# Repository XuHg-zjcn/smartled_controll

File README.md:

# 智能LED控制器
该LED控制器用于吸顶灯、灯带、台灯的控制，使用12-48V电源供电(使用Buck驱动，电源电压必须高于灯的电压)，使用经过编码的RS485通信。计划PCB采用双面板，板上最多可焊4个LED驱动电路
待添加多种设计，分别支持4通道和2通道
需要添加外接声感（驻极体麦克风），雷达，（热释电）红外线等传感器检测下亮灯

经过平衡安全性、稳定性、传输效率、可扩展性、总成本等因素的考量，我设计家庭小功率电器总线采用不超过直流60V的SELV供电。使用两根直流电源线（不接地）和一对差分通信线。  
为了防止通信线(RS485)误接电源线造成过压等原因导致芯片等元器件损坏，我参考网上资料设计了一套保护电路。其中甚至牺牲了一些兼容性，让数据经过直流平衡的编码后再传输，这样信号能顺利通过电容，误接直流电时后面电路只有一个脉冲，大大减轻TVS管负荷。  

# 主要元器件列表
|  名称  |     型号     |    参数     |
|:------:|:-------------|:------------|
|MCU     |候选PY32F003F1|QFN20封装    |
|DCDC转换|OC5864        |最高60V输入, 0.6A|
|LED驱动 |OC5028B/OC5020B|100V 1.2A/2A|
|通信芯片|候选MAX485    |最高2.5Mbps  |

其他元器件请通过KiCAD生成BOM表获取

# 构建PCB工程
为了减少git仓库占用空间，我在`git commit`提交前在KiCad中清除所有填充域(快捷键Ctrl+B)，您可以在打开后重新填充(快捷键B)
在KiCad的Python控制台中，切换到该repo根目录运行下例命令
````python
import build
build.all()
```
即可自动完成添加泪滴、重新填充、应用PCB背面信息字符串

# 版权和许可证
Copyright (C) 2025  徐瑞骏  
本设计以CERN开放硬件许可证第二版强互惠授权(CERN Open Hardware Licence Version 2 - Strongly Reciprocal)，许可证文件位于`cern_ohl_s_v2.txt`  
本设计不提供任何保证

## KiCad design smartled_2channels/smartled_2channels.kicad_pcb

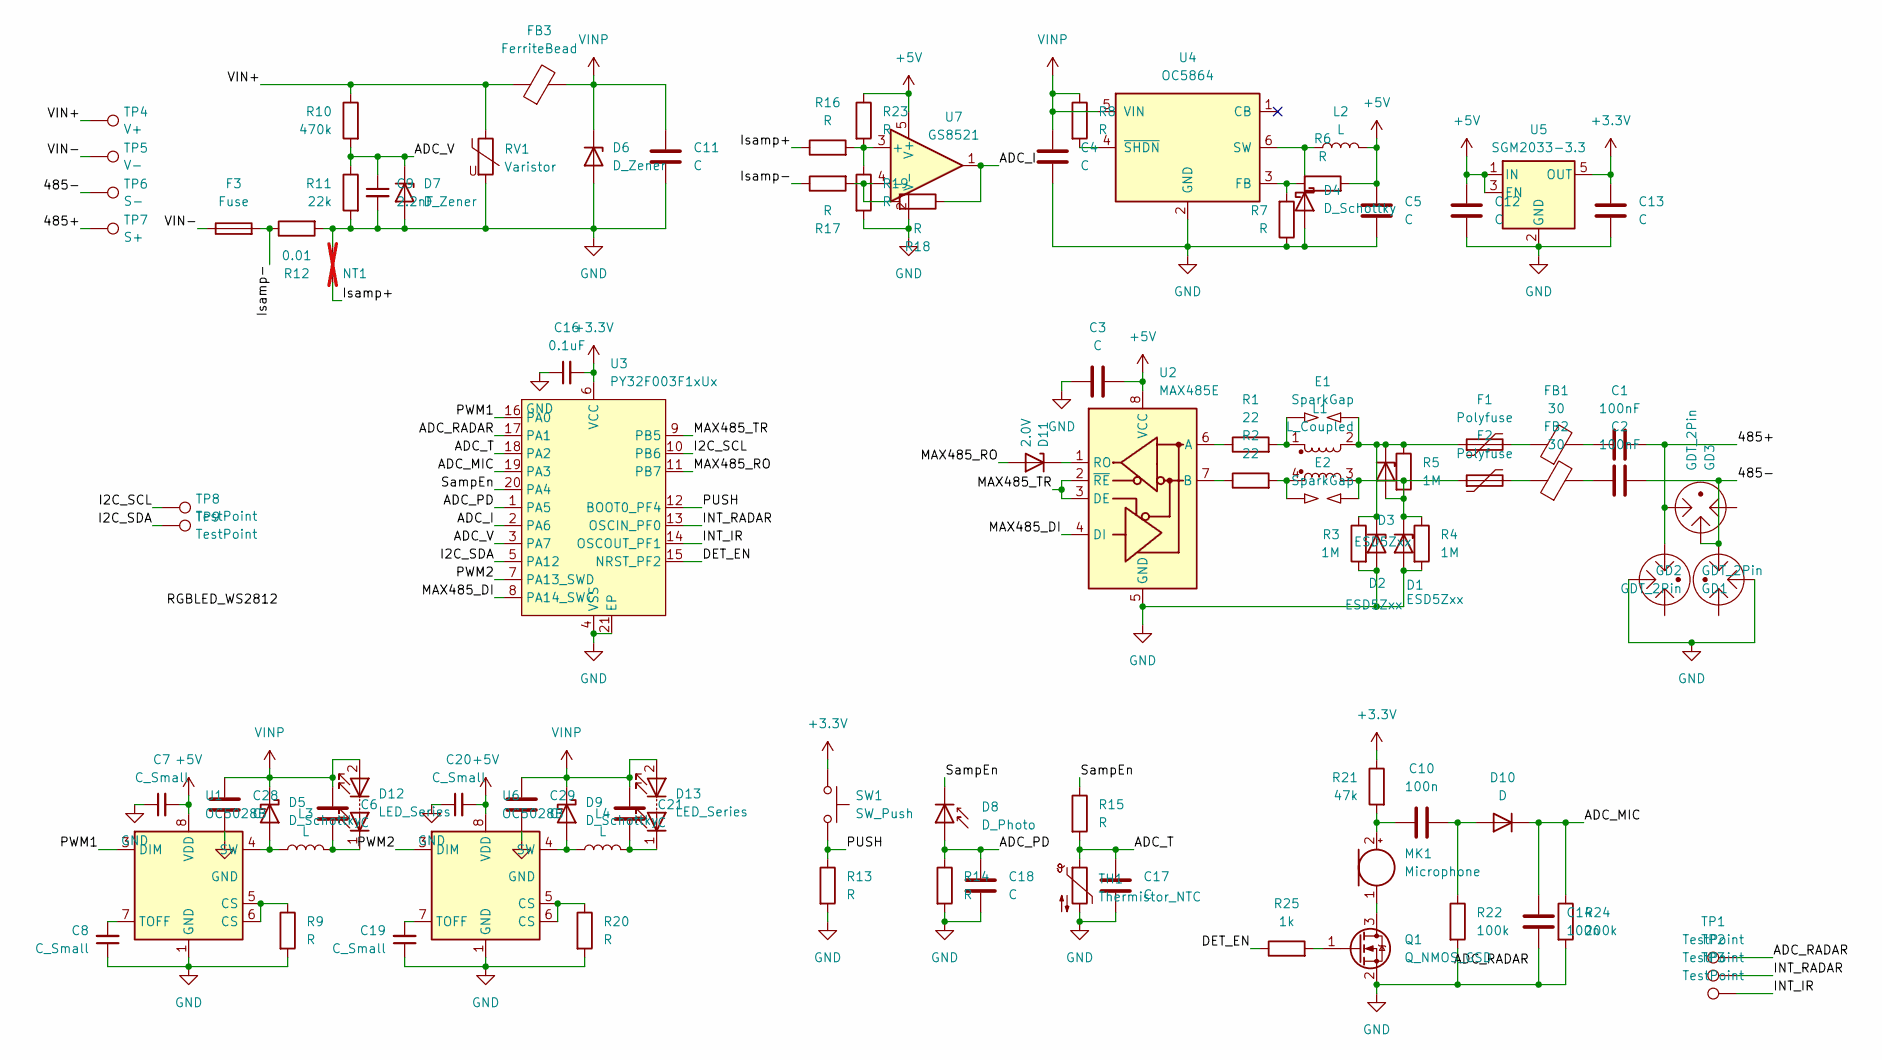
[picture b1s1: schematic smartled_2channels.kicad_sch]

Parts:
C1, C2: 100nF; C_0603_1608Metric
C3: C; C_0603_1608Metric
C4, C5, C12, C13: C; C_0805_2012Metric
C6, C11, C21, C28, C29: C; C_1210_3225Metric
C7, C8, C19, C20: C_Small; C_0402_1005Metric
C9: 2.2nF; C_0603_1608Metric
C10, C14: 100n; C_0402_1005Metric
C16: 0.1uF; C_0603_1608Metric
C17, C18: C; C_0402_1005Metric
D1, D2, D3: ESD5Zxx; D_SOD-523
D4: D_Schottky; D_SOD-123F
D5, D9: D_Schottky; D_SMA
D6: D_Zener; D_SMA
D7: D_Zener; D_SOD-323
D8: D_Photo; D_0805_2012Metric
D10: D; D_SOD-523
D11: 2.0V; D_SOD-523
D12, D13: LED_Series; 2Pads_1.5x2.7mm_Tshape_mpsign
E1, E2: SparkGap
F1, F2: Polyfuse; Fuse_0603_1608Metric
F3: Fuse; Fuse_1206_3216Metric
FB1, FB2: 30; L_0603_1608Metric
FB3: FerriteBead; L_1210_3225Metric
GD1, GD2, GD3: GDT_2Pin; C_1206_3216Metric
L1: L_Coupled; L_CommonModeChoke_Coilcraft_1812CAN
L2: L; L_1210_3225Metric
L3, L4: L; L_APV_APH0630
MK1: Microphone; D_SOD-323
NT1: NetTie_2; NetTie-2_VIA_Pad0.6_0.3mm; not fitted
Q1: Q_NMOS_GSD; SOT-23
R1, R2: 22; R_0603_1608Metric
R3, R4, R5: 1M; R_0603_1608Metric
R6, R7, R8, R13, R14, R15, R16, R17, R18, R19, R23: R; R_0402_1005Metric
R9, R20: R; R_1206_3216Metric
R10: 470k; R_0603_1608Metric
R11: 22k; R_0603_1608Metric
R12: 0.01; R_1206_3216Metric
R21: 47k; R_0402_1005Metric
R22: 100k; R_0603_1608Metric
R24: 200k; R_0402_1005Metric
R25: 1k; R_0402_1005Metric
RV1: Varistor; R_1206_3216Metric
SW1: SW_Push; SW_Push_SPST_NO_Alps_SKRK
TH1: Thermistor_NTC; R_0805_2012Metric
TP1, TP2, TP3, TP8, TP9: TestPoint; 1Pad_0.6mm
TP4: V+; TestPoint_THTPad_D1.0mm_Drill0.5mm
TP5: V-; TestPoint_THTPad_D1.0mm_Drill0.5mm
TP6: S-; TestPoint_THTPad_D1.0mm_Drill0.5mm
TP7: S+; TestPoint_THTPad_D1.0mm_Drill0.5mm
U1, U6: OC5028B; HSOP-8-1EP_3.9x4.9mm_P1.27mm_EP2.41x3.1mm_ThermalVias_0.3_0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
U2: MAX485E; SOIC-8_3.9x4.9mm_P1.27mm
U3: PY32F003F1xUx; QFN-20-1EP_3x3mm_P0.4mm_EP1.65x1.65mm
U4: OC5864; SOT-23-6
U5: SGM2033-3.3; SOT-23-5
U7: GS8521; TSOT-23-5

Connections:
+3.3V: C13.1, C16.2, R21.1, SW1.1, U3.6 (VCC), U5.5 (OUT)
+5V: C3.2, C5.1, C7.2, C12.1, C20.2, L2.2, R6.2, R23.1, U1.8 (VDD), U2.8 (VCC), U5.1 (IN), U5.3 (EN), U6.8 (VDD), U7.5 (V+)
/485+: C1.2, GD1.1, GD3.1, TP7.1
/485-: C2.2, GD2.1, GD3.2, TP6.1
/ADC_I: R18.1, U3.2 (PA6), U7.1
/ADC_MIC: C14.1, D10.1 (K), R24.1, U3.19 (PA3)
/ADC_PD: C18.1, D8.2 (A), R14.1, U3.1 (PA5)
/ADC_RADAR: TP1.1, U3.17 (PA1)
/ADC_T: C17.1, R15.2, TH1.1, U3.18 (PA2)
/ADC_V: C9.1, D7.1 (K), R10.2, R11.1, U3.3 (PA7)
/DET_EN: R25.1, U3.15 (NRST_PF2)
/I2C_SCL: TP8.1, U3.10 (PB6)
/I2C_SDA: TP9.1, U3.5 (PA12)
/INT_IR: TP3.1, U3.14 (OSCOUT_PF1)
/INT_RADAR: TP2.1, U3.13 (OSCIN_PF0)
/Isamp+: NT1.2, R16.1
/Isamp-: F3.2, R12.1, R17.1
/MAX485_DI: U2.4 (DI), U3.8 (PA14_SWC)
/MAX485_RO: D11.2 (A), U3.11 (PB7)
/MAX485_TR: U2.2 (~RE), U2.3 (DE), U3.9 (PB5)
/PUSH: R13.1, SW1.2, U3.12 (BOOT0_PF4)
/PWM1: U1.3 (DIM), U3.16 (PA0)
/PWM2: U3.7 (PA13_SWD), U6.3 (DIM)
/SampEn: D8.1 (K), R15.1, U3.20 (PA4)
/VIN+: FB3.1, R10.1, RV1.1, TP4.1
/VIN-: F3.1, TP5.1
GND: C3.1, C4.1, C5.2, C7.1, C8.1, C9.2, C11.2, C12.2, C13.2, C14.2, C16.1, C17.2, C18.2, C19.1, C20.1, C28.1, C29.1, D1.2 (A), D2.2 (A), D4.2 (A), D6.2 (A), D7.2 (A), GD1.2, GD2.2, NT1.1, Q1.2 (S), R3.2, R4.2, R7.1, R9.2, R11.2, R12.2, R13.2, R14.2, R19.2, R20.2, R22.2, R24.2, RV1.2, TH1.2, U1.1 (GND), U2.5 (GND), U3.4 (VSS), U3.21 (EP), U4.2 (GND), U5.2 (GND), U6.1 (GND), U7.2 (V-)
unnamed: C1.1, FB1.2
unnamed: C2.1, FB2.2
unnamed: D1.1 (K), D3.2 (A), E2.2, F2.1, L1.3, R4.1, R5.2
unnamed: D2.1 (K), D3.1 (K), E1.2, F1.1, L1.2, R3.1, R5.1
unnamed: D4.1 (K), L2.1, U4.6 (SW)
unnamed: D5.2 (A), L3.1, U1.4 (SW), U1.9 (EP)
unnamed: D9.2 (A), L4.1, U6.4 (SW), U6.9 (EP)
unnamed: C10.2, D10.2 (A), R22.1
unnamed: D11.1 (K), U2.1 (RO)
unnamed: C6.2, D12.1 (K), L3.2
unnamed: C21.2, D13.1 (K), L4.2
unnamed: E1.1, L1.1, R1.2
unnamed: E2.1, L1.4, R2.2
unnamed: F1.2, FB1.1
unnamed: F2.2, FB2.1
unnamed: C10.1, MK1.2 (+), R21.2
unnamed: MK1.1 (-), Q1.3 (D)
unnamed: Q1.1 (G), R25.2
unnamed: R9.1, U1.5 (CS), U1.6 (CS)
unnamed: R20.1, U6.5 (CS), U6.6 (CS)
unnamed: C8.2, U1.7 (TOFF)
unnamed: R1.1, U2.6 (A)
unnamed: R2.1, U2.7 (B)
unnamed: R6.1, R7.2, U4.3 (FB)
unnamed: R8.2, U4.4 (~SHDN)
unnamed: C19.2, U6.7 (TOFF)
unnamed: R16.2, R19.1, R23.2, U7.3 (+)
unnamed: R17.2, R18.2, U7.4 (-)
VINP: C4.2, C6.1, C11.1, C21.1, C28.2, C29.2, D5.1 (K), D6.1 (K), D9.1 (K), D12.2 (A), D13.2 (A), FB3.2, R8.1, U4.5 (VIN)

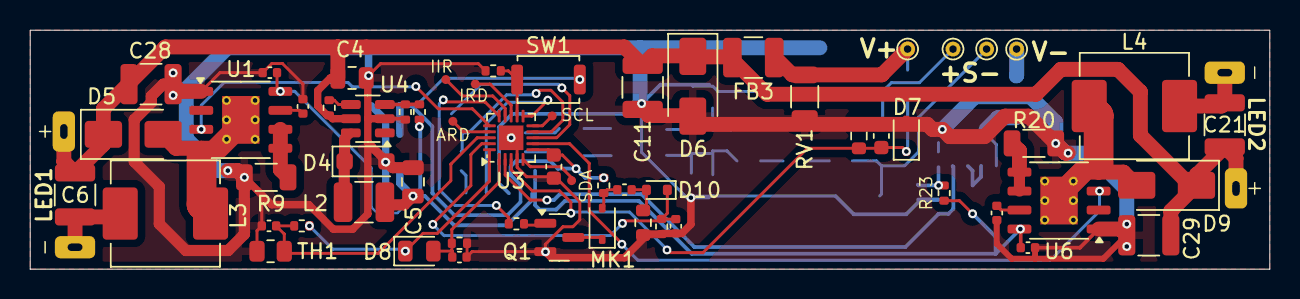
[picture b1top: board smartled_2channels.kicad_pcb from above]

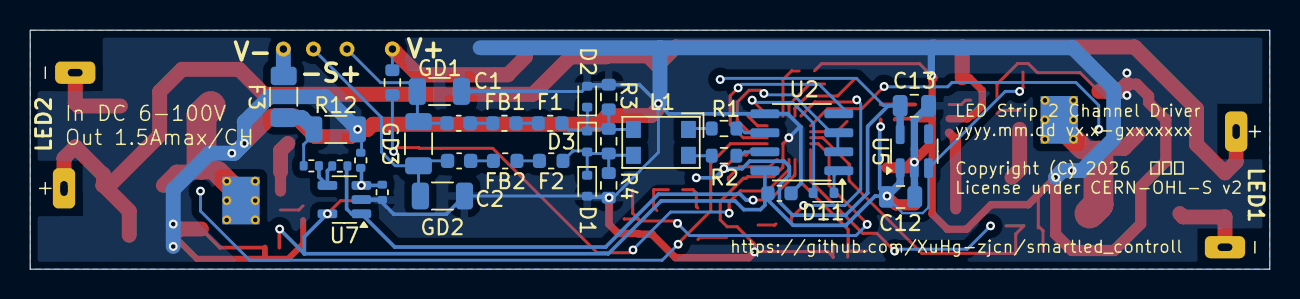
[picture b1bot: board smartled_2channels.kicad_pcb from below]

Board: 2 copper layers, 83.0 x 16.0 mm, 94 parts (32 on the bottom side), 55 nets.

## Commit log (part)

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2025-02-23 添加README.md和CERN-OHL-S许可证
2025-02-23 单片机换为PY32F003F1xUx（自己制作符号），添加3.3V LDO电路，电流采样放大电路，按键，温度和光照传感器
2025-02-24 在PCB上放置各电路模块的元器件大致布局，少量修改原理图
2025-02-25 布线和调整布局，把PCB上的电路按模块分组
2025-02-26 复制LED驱动模块为4个
2025-02-26 布线和微调布局（除光电二极管和温度传感器外）
2025-02-27 调整布局，划出PCB边框，MCU连接光电二极管和温度传感器
2025-02-27 添加GND,VINP等覆铜（提交前已清除填充来减小文件大小，请在KiCAD重新填充）
2025-02-27 修复DRC错误，调整位号等
2025-03-01 添加LED驱动输入滤波电容(1210封装)
2025-03-01 添加I2C接口
2025-03-01 按照数据手册将PY32中心焊盘接GND
2025-03-02 PCB上添加接口定义和版权声明文本
2025-03-02 按OC5028B数据手册将第二脚NC改成不连接
2025-03-09 在RS485的两条差分线间再添加一个气体放电管，都改为1206封装
2025-03-10 保险丝改成2410(6125)封装
2025-03-10 选择3.3V LDO和电流采样运放的型号
2025-03-10 添加LED接口焊盘
2025-03-10 添加LED接口编号丝印
2025-03-12 优化3D图效果：隐藏借用footprint而产生不正确的3D模型
2025-03-12 PCB上添加说明文本，从其他工程复制build.py脚本
2025-04-29 提交遗留内容，添加圆角和安装孔
2025-04-29 设置PCB工程的最小间距、最小走线宽度和最小连接宽度，最小线宽改成0.16mm
2026-05-20 现有工程移动移动到4channels目录下，更新README.md
2026-05-20 添加2通道驱动器工程，从4通道驱动器复制部分内容并进行大致布局
2026-05-20 添加麦克风声感应电路，红外和雷达传感器接口
2026-05-22 压缩布局至85.4x16mm尺寸
2026-05-24 进行布线，微调原理图
2026-05-26 连接一些未连接项目
2026-05-29 修改LED输出焊盘，缩短PCB长度到83mm
2026-05-30 修改丝印
2026-05-30 修复一些DRC错误，优化布线
2026-05-30 电源和通信端口放置通孔焊盘用于焊接电线
2026-05-31 修改TP焊盘为0.6mm，引出I2C接口
2026-05-31 修改LED输出接口为通孔焊盘
2026-05-31 保险丝移动到负极
2026-06-07 MAX485 RO添加稳压二极管做电平转换

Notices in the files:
smartled_2channels/smartled_2channels.kicad_pcb:
Copyright (C) 2026  徐瑞骏
License under CERN-OHL-S v2
